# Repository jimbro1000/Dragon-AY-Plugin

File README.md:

# AY(ish) Plugin For Dragon32 Rev 3 #

This repository contains the design for an emulated AY8910/2/3 
plugin board to fit the Dragon32 Rev3 boards.

The design is based on the avr-ay designs using an Atmega MCU

The design does not support the PIO capabilities of the
original AY8910/2, providing only the sound generation

The footprint is a significant departure using a largish
plcc style footprint but thanks to a lack of support in
KiCad this has come out larger than intended

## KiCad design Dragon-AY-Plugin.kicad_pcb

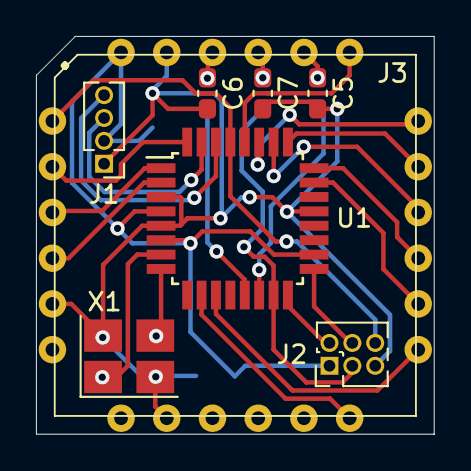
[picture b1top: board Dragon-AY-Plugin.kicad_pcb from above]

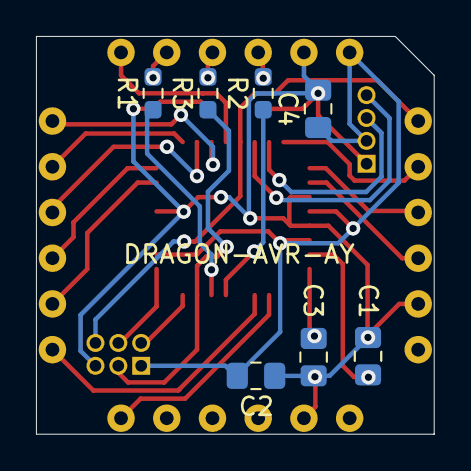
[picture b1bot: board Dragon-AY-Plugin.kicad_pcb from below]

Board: 2 copper layers, 22.1 x 22.1 mm, 15 parts (7 on the bottom side), 26 nets.

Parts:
C1, C3: 18pF; C_0805_2012Metric_Pad1.18x1.45mm_HandSolder
C2, C4: 100nF; C_0805_2012Metric_Pad1.18x1.45mm_HandSolder
C5, C6, C7: 2.2nF; C_0603_1608Metric_Pad1.08x0.95mm_HandSolder
J1: UART; PinHeader_1x04_P1.27mm_Vertical
J2: ICSP; PinHeader_2x03_P1.27mm_Vertical
J3: Conn_01x24; AY-QTHT
R1, R2, R3: 3.6K; R_0603_1608Metric_Pad0.98x0.95mm_HandSolder
U1: ATmega48PA-A; TQFP-32_7x7mm_P0.8mm
X1: 27MHz; Crystal_SMD_3225-4Pin_3.2x2.5mm_HandSoldering

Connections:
+5V: C2.1, C4.1, J1.2, J2.1, J3.1, U1.4 (VCC), U1.6 (VCC), U1.18 (AVCC)
BC1: J3.23, U1.32 (PD2)
BDIR: J3.22, U1.1 (PD3)
CLOCK: J3.21, U1.2 (PD4)
D0: J3.11, U1.23 (PC0)
D1: J3.10, U1.24 (PC1)
D2: J3.8, U1.25 (PC2)
D3: J3.9, U1.26 (PC3)
D4: J3.7, U1.27 (PC4)
D5: J3.6, U1.28 (PC5)
D6: J3.13, U1.10 (PD6)
D7: J3.12, U1.11 (PD7)
GND: C1.2, C2.2, C3.2, C4.2, C5.2, C6.2, C7.2, J1.1, J2.5, J3.2, J3.17, J3.20, U1.3 (GND), U1.5 (GND), U1.21 (GND), X1.2, X1.4
MISO: J2.2, U1.16 (PB4)
MOSI: J2.3, R3.1, U1.15 (PB3)
OUT_A: C6.1, J3.3, R2.2
OUT_B: C7.1, J3.4, R3.2
OUT_C: C5.1, J3.5, R1.2
PWM_A: R2.1, U1.13 (PB1)
PWM_C: R1.1, U1.14 (PB2)
RX: J1.4, U1.30 (PD0)
SCK: J2.4, U1.17 (PB5)
TX: J1.3, U1.31 (PD1)
XTAL1: C1.1, U1.7 (XTAL1/PB6), X1.1
XTAL2: C3.1, U1.8 (XTAL2/PB7), X1.3
~RES: J2.6, J3.24, U1.29 (~RESET/PC6)
